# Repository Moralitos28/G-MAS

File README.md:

# G-MAS
 Grandpa - Movement Asistent System

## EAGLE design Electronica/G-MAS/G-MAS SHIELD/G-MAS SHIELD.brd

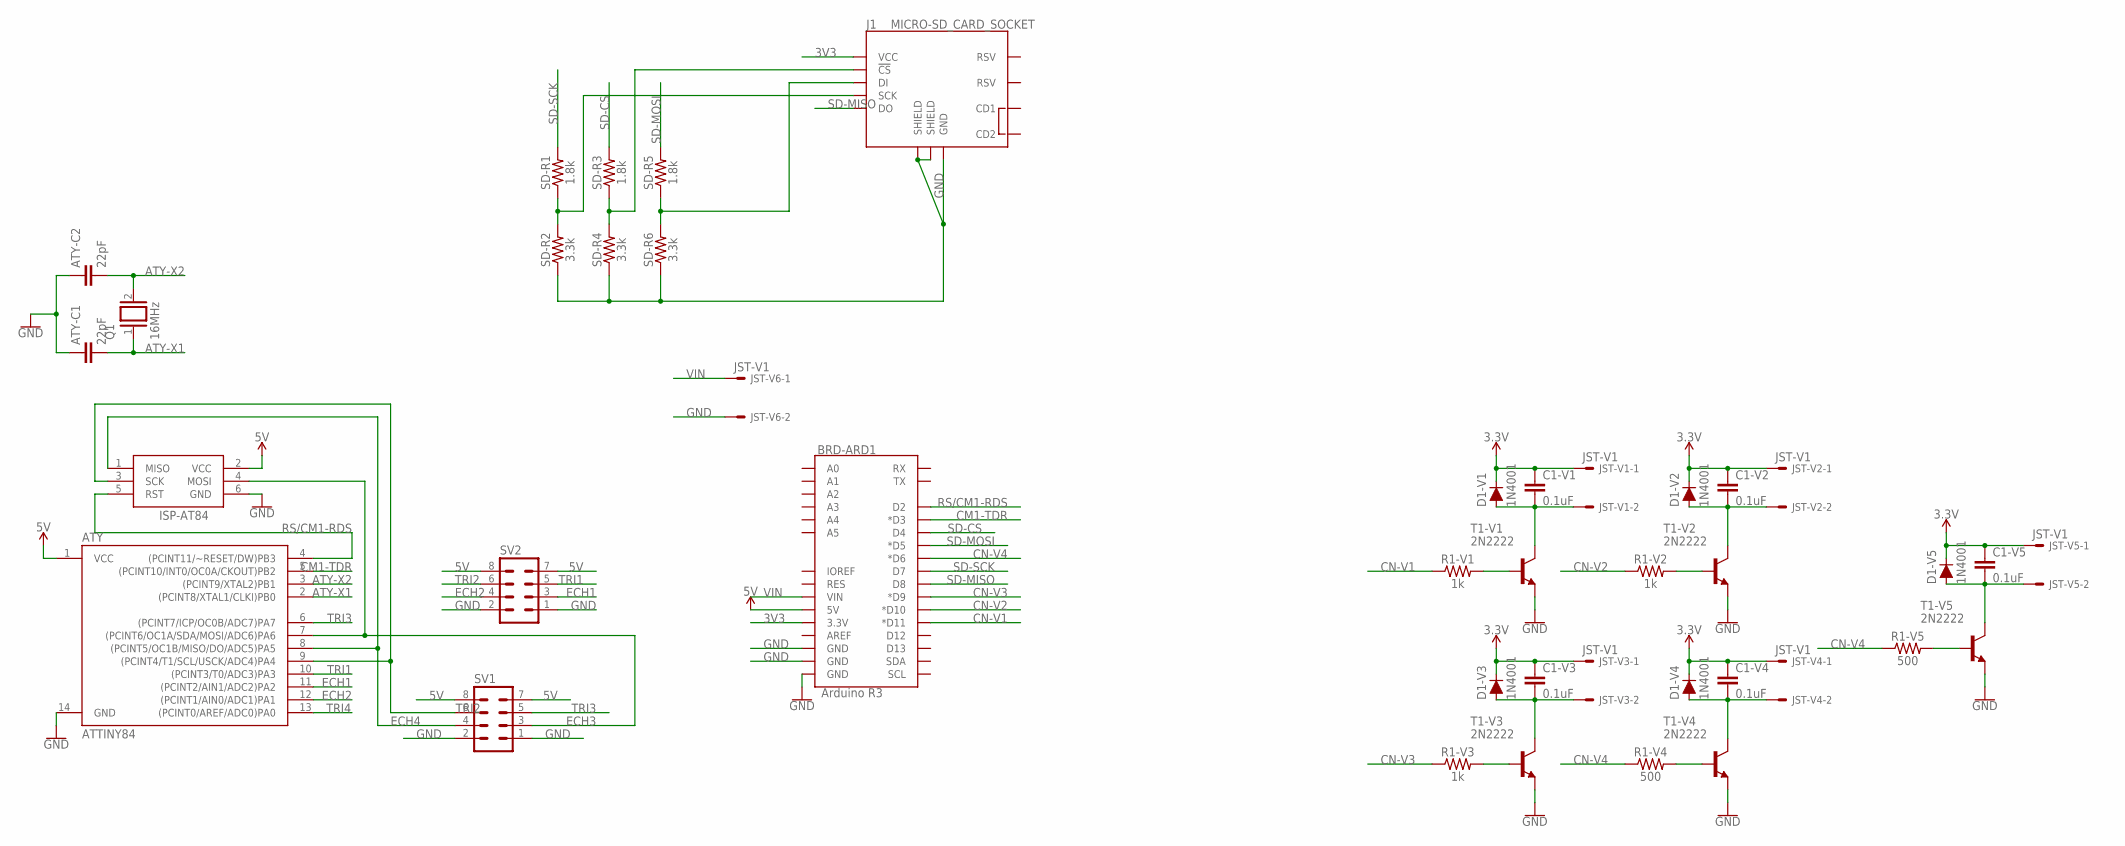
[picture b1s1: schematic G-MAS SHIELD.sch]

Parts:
ATY: ATTINY84; DIP14
ATY-C1, ATY-C2: 22pF; CAP-PTH-SMALL-KIT
BRD-ARD1: Arduino R3; UNO_R3_SHIELD_NOLABELS
C1-V1, C1-V2, C1-V3, C1-V4, C1-V5: 0.1uF; CAP-PTH-SMALL-KIT
D1-V1, D1-V2, D1-V3, D1-V4, D1-V5: 1N4001; DIODE-1N4001
ISP-AT84: AVRISP-6; AVRISP
J1: MICRO-SD_CARD_SOCKET; MICRO-SD-SOCKET
JST-V1, JST-V2, JST-V3, JST-V4, JST-V5, JST-V6: JST-V1; JST-XH-02-PACKAGE-LONG-PAD
Q1: 16MHz; QS
R1-V1, R1-V2, R1-V3: 1k; AXIAL-0.3
R1-V4, R1-V5: 500; AXIAL-0.3
SD-R1, SD-R3, SD-R5: 1.8k; 0603
SD-R2, SD-R4, SD-R6: 3.3k; 0603
SV1, SV2: MA04-2
T1-V1, T1-V2, T1-V3, T1-V4, T1-V5: 2N2222; TO92-EBC-OVAL

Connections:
3.3V: C1-V1.1, C1-V2.1, C1-V3.1, C1-V4.1, C1-V5.1, D1-V1.C, D1-V2.C, D1-V3.C, D1-V4.C, D1-V5.C, JST-V1.1, JST-V2.1, JST-V3.1, JST-V4.1, JST-V5.1
3V3: BRD-ARD1.3.3V, J1.VCC
5V: ATY.1 (VCC), BRD-ARD1.5V, ISP-AT84.2 (VCC), SV1.7, SV1.8, SV2.7, SV2.8
ATY-X1: ATY.2 ((PCINT8/XTAL1/CLKI)PB0), ATY-C1.2, Q1.1
ATY-X2: ATY.3 ((PCINT9/XTAL2)PB1), ATY-C2.2, Q1.2
CM1-TDR: ATY.5 ((PCINT10/INT0/OC0A/CKOUT)PB2), BRD-ARD1.D3 (*D3)
CN-V1: BRD-ARD1.D11 (*D11), R1-V1.P$1 (1)
CN-V2: BRD-ARD1.D10 (*D10), R1-V2.P$1 (1)
CN-V3: BRD-ARD1.D9 (*D9), R1-V3.P$1 (1)
CN-V4: BRD-ARD1.D6 (*D6), R1-V4.P$1 (1), R1-V5.P$1 (1)
ECH1: ATY.11 ((PCINT2/AIN1/ADC2)PA2), SV2.3
ECH2: ATY.12 ((PCINT1/AIN0/ADC1)PA1), SV2.4
ECH3: ATY.7 ((PCINT6/OC1A/SDA/MOSI/ADC6)PA6), ISP-AT84.4 (MOSI), SV1.3
ECH4: ATY.8 ((PCINT5/OC1B/MISO/DO/ADC5)PA5), ISP-AT84.1 (MISO), SV1.4
GND: ATY.14 (GND), ATY-C1.1, ATY-C2.1, BRD-ARD1.GND@0 (GND), BRD-ARD1.GND@1 (GND), BRD-ARD1.GND@2 (GND), ISP-AT84.6 (GND), J1.GND, J1.GND1 (SHIELD), J1.GND3 (SHIELD), JST-V6.2, SD-R2.1, SD-R4.1, SD-R6.1, SV1.1, SV1.2, SV2.1, SV2.2, T1-V1.E, T1-V2.E, T1-V3.E, T1-V4.E, T1-V5.E
unnamed: C1-V1.2, D1-V1.A, JST-V1.2, T1-V1.C
unnamed: C1-V2.2, D1-V2.A, JST-V2.2, T1-V2.C
unnamed: R1-V1.P$2 (2), T1-V1.B
unnamed: R1-V2.P$2 (2), T1-V2.B
unnamed: C1-V3.2, D1-V3.A, JST-V3.2, T1-V3.C
unnamed: R1-V3.P$2 (2), T1-V3.B
unnamed: C1-V4.2, D1-V4.A, JST-V4.2, T1-V4.C
unnamed: R1-V4.P$2 (2), T1-V4.B
unnamed: C1-V5.2, D1-V5.A, JST-V5.2, T1-V5.C
unnamed: R1-V5.P$2 (2), T1-V5.B
unnamed: J1.SCLK (SCK), SD-R1.1, SD-R2.2
unnamed: J1.CS (!CS), SD-R3.1, SD-R4.2
unnamed: J1.DI, SD-R5.1, SD-R6.2
RS/CM1-RDS: ATY.4 ((PCINT11/~RESET/DW)PB3), BRD-ARD1.D2, ISP-AT84.5 (RST)
SD-CS: BRD-ARD1.D4, SD-R3.2
SD-MISO: BRD-ARD1.D8, J1.DO
SD-MOSI: BRD-ARD1.D5 (*D5), SD-R5.2
SD-SCK: BRD-ARD1.D7, SD-R1.2
TRI1: ATY.10 ((PCINT3/T0/ADC3)PA3), SV2.5
TRI2: ATY.13 ((PCINT0/AREF/ADC0)PA0), SV2.6
TRI3: ATY.6 ((PCINT7/ICP/OC0B/ADC7)PA7), SV1.5
TRI4: ATY.9 ((PCINT4/T1/SCL/USCK/ADC4)PA4), ISP-AT84.3 (SCK), SV1.6
VIN: BRD-ARD1.VIN, JST-V6.1

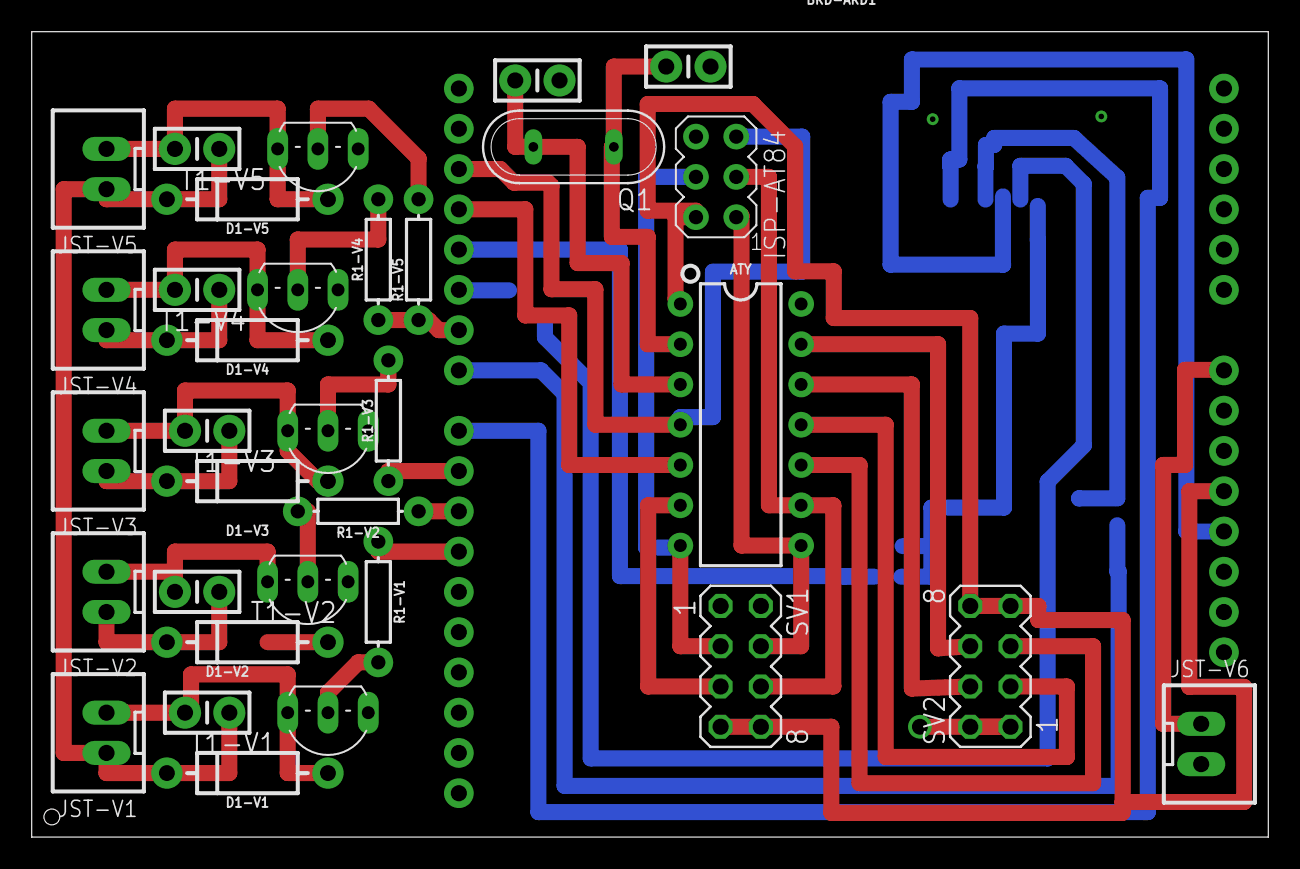
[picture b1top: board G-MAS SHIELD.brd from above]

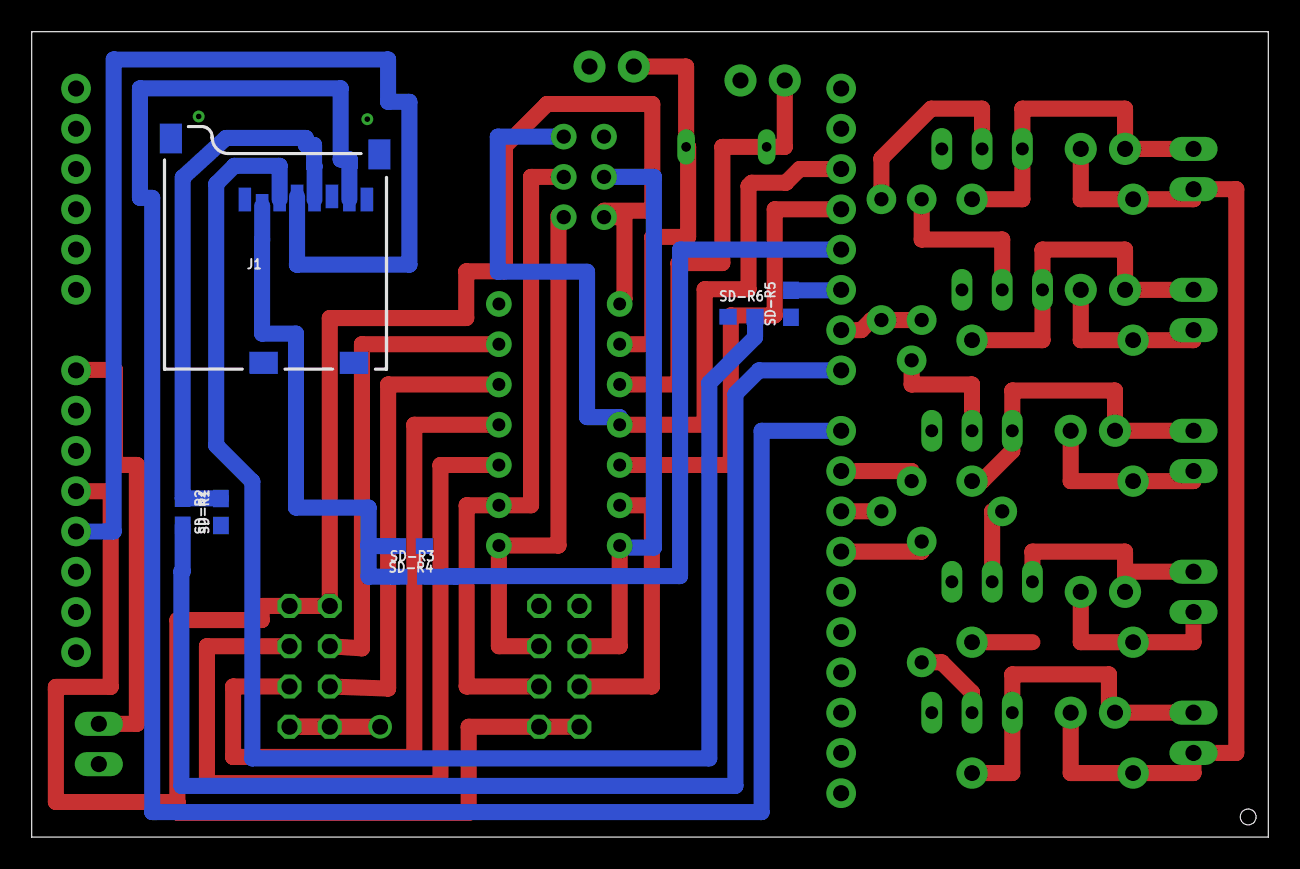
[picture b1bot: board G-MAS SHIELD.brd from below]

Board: 2 copper layers, 78.0 x 50.8 mm, 41 parts (7 on the bottom side), 38 nets.

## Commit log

2019-07-23 Genesis Commit
    Initial Real Commit
2019-07-27 Control De Vibradores
    Control de vibradores
2019-07-28 Vibration Sensor Module
    Incorpotation of the first version of the sensor module, beta, using attiny84.
2019-08-26 V1
    Incorporacion de MicroSD

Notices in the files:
parts and their libraries:
SparkFun-Boards: Licensing: Creative Commons ShareAlike 4.0 International - https://creativecommons.org/licenses/by-sa/4.0
